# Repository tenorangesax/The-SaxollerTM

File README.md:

# The-Saxoller™
A simple art shortcut keyboard for digital artists! (like me!) Includes 12 keyboard switches that can be programmed to do any shortcuts, a rotary encoder for zooming canvases, and powered by a ESP32C3 Seeed Studio!

**3D VIEWER:**

**SCHEMATIC:**

**PCB EDITOR:**

**BOM:**

| Item name | Quantity | Single price | Link to purchase | Description |
|---|---:|---:|---|---|
| Cherry MX-compatible PCB switch | 12 | $0.40 | [MechanicalKeyboards](https://mechanicalkeyboards.com/products/cherry-mx-honey-silent-45g-tactile-pcb-mount-switch) | Keyboard switches for the 12 keys |
| Rotary encoder with push switch | 1 | $4.90 | [Amazon](https://www.amazon.com/WWZMDiB-Encoder-Digital-Potentiometer-Arduino/dp/B0C6Q67V97?s=industrial) | Rotary input control |
| ESP32C3 Seeed Studio | 1 | $10.00 | [Amazon](https://www.amazon.com/HiLetgo-ESP-WROOM-32-Development-Microcontroller-Integrated/dp/B0718T232Z?s=industrial](https://www.amazon.com/Seeed-Studio-XIAO-ESP32C3-Microcontroller/dp/B0B94JZ2YF?th=1)) | Main controller board |

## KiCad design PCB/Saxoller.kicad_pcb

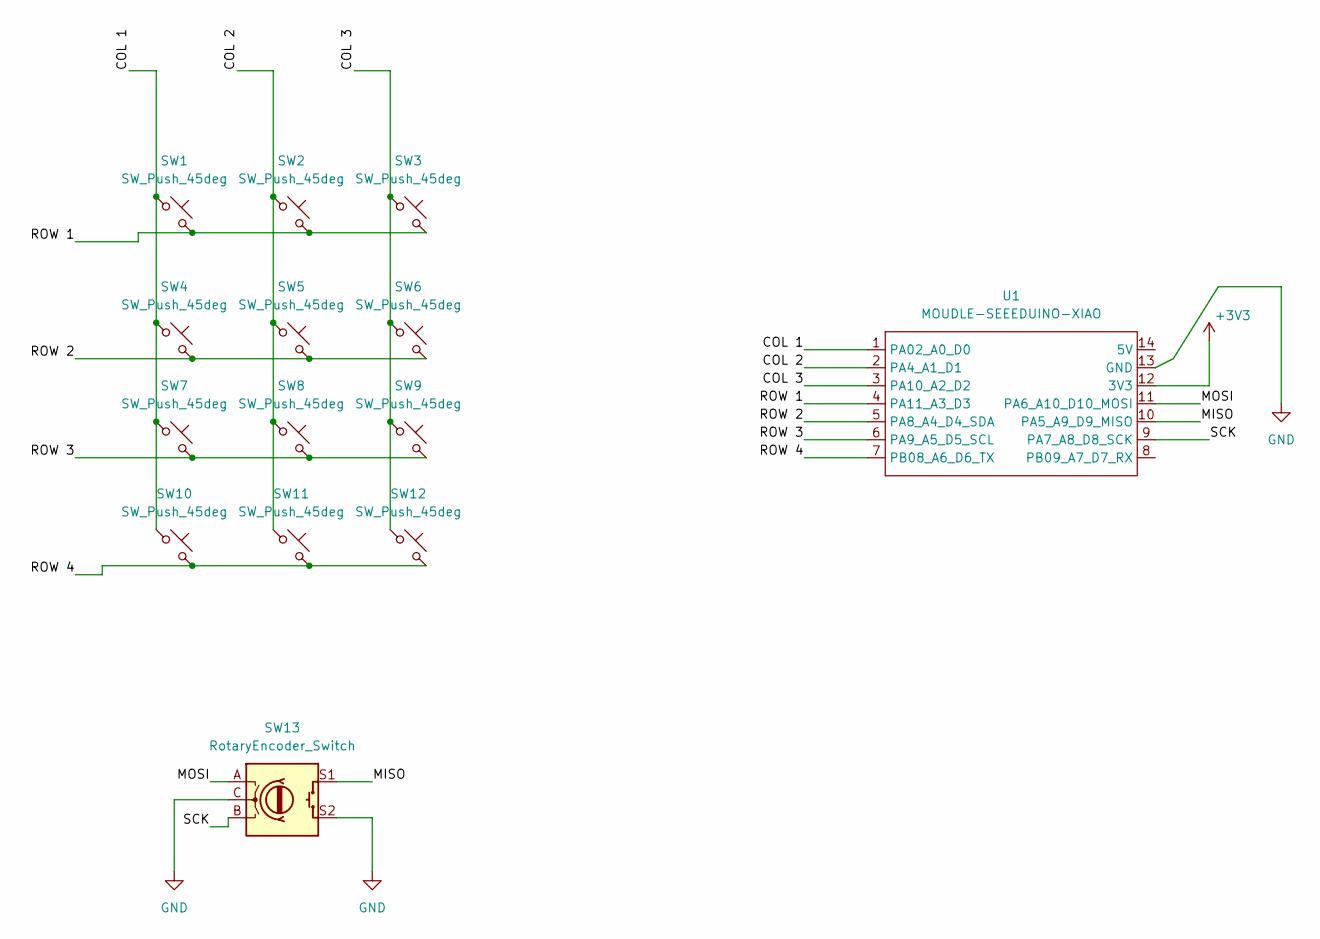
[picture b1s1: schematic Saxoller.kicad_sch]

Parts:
SW1, SW2, SW3, SW4, SW5, SW6, SW7, SW8, SW9, SW10, SW11, SW12: SW_Push_45deg; SW_Cherry_MX_1.00u_PCB
SW13: RotaryEncoder_Switch; RotaryEncoder_Alps_EC11E-Switch_Vertical_H20mm
U1: MOUDLE-SEEEDUINO-XIAO; MCU_Seeed_ESP32C3

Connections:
+3V3: U1.12 (3V3)
/COL 1: SW1.1, SW4.1, SW7.1, SW10.1, U1.1 (PA02_A0_D0)
/COL 2: SW2.1, SW5.1, SW8.1, SW11.1, U1.2 (PA4_A1_D1)
/COL 3: SW3.1, SW6.1, SW9.1, SW12.1, U1.3 (PA10_A2_D2)
/MISO: SW13.S1, U1.10 (PA5_A9_D9_MISO)
/MOSI: SW13.A, U1.11 (PA6_A10_D10_MOSI)
/ROW 1: SW1.2, SW2.2, SW3.2, U1.4 (PA11_A3_D3)
/ROW 2: SW4.2, SW5.2, SW6.2, U1.5 (PA8_A4_D4_SDA)
/ROW 3: SW7.2, SW8.2, SW9.2, U1.6 (PA9_A5_D5_SCL)
/ROW 4: SW10.2, SW11.2, SW12.2, U1.7 (PB08_A6_D6_TX)
/SCK: SW13.B, U1.9 (PA7_A8_D8_SCK)
GND: SW13.C, SW13.S2, U1.13 (GND)

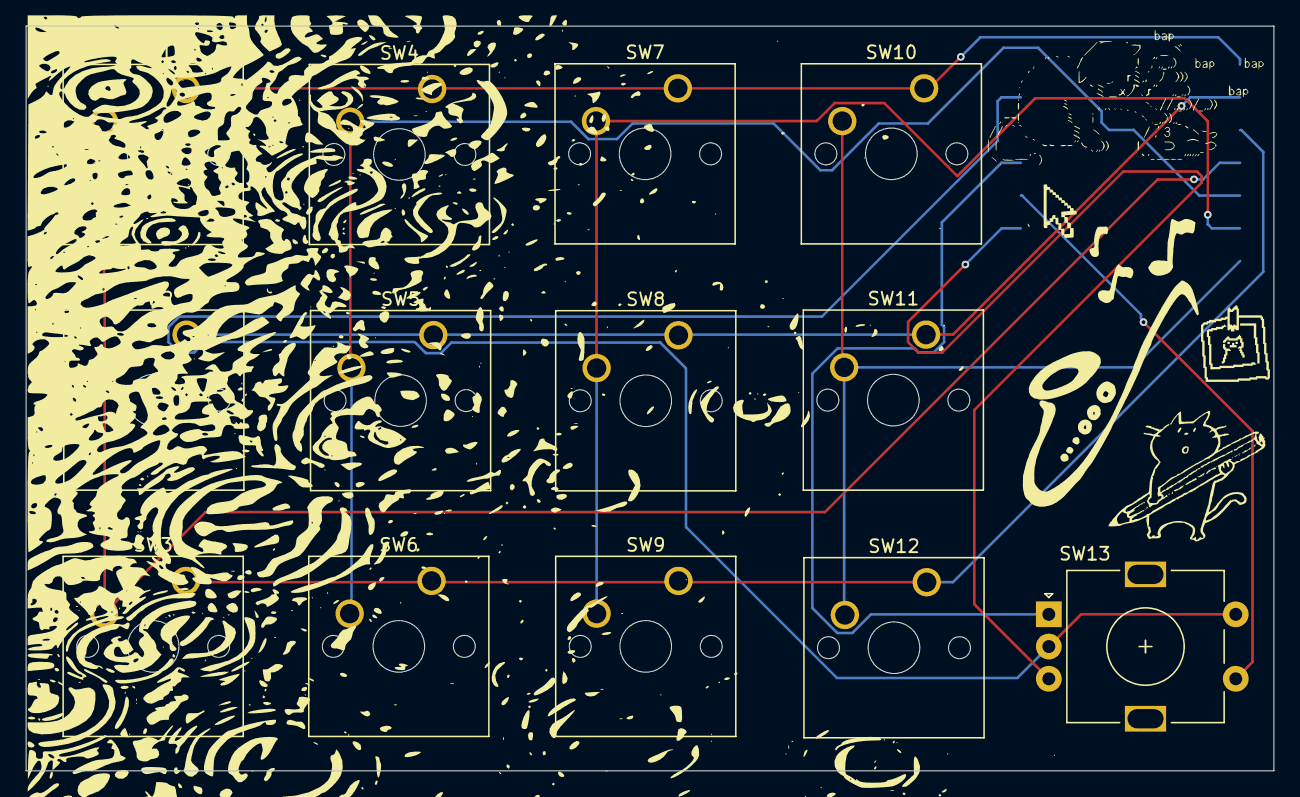
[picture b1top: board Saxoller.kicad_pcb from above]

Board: 2 copper layers, 96.8 x 57.8 mm, 14 parts (1 on the bottom side), 11 nets.
